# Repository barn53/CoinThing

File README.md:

# WhaleTicker
a coin ticker display

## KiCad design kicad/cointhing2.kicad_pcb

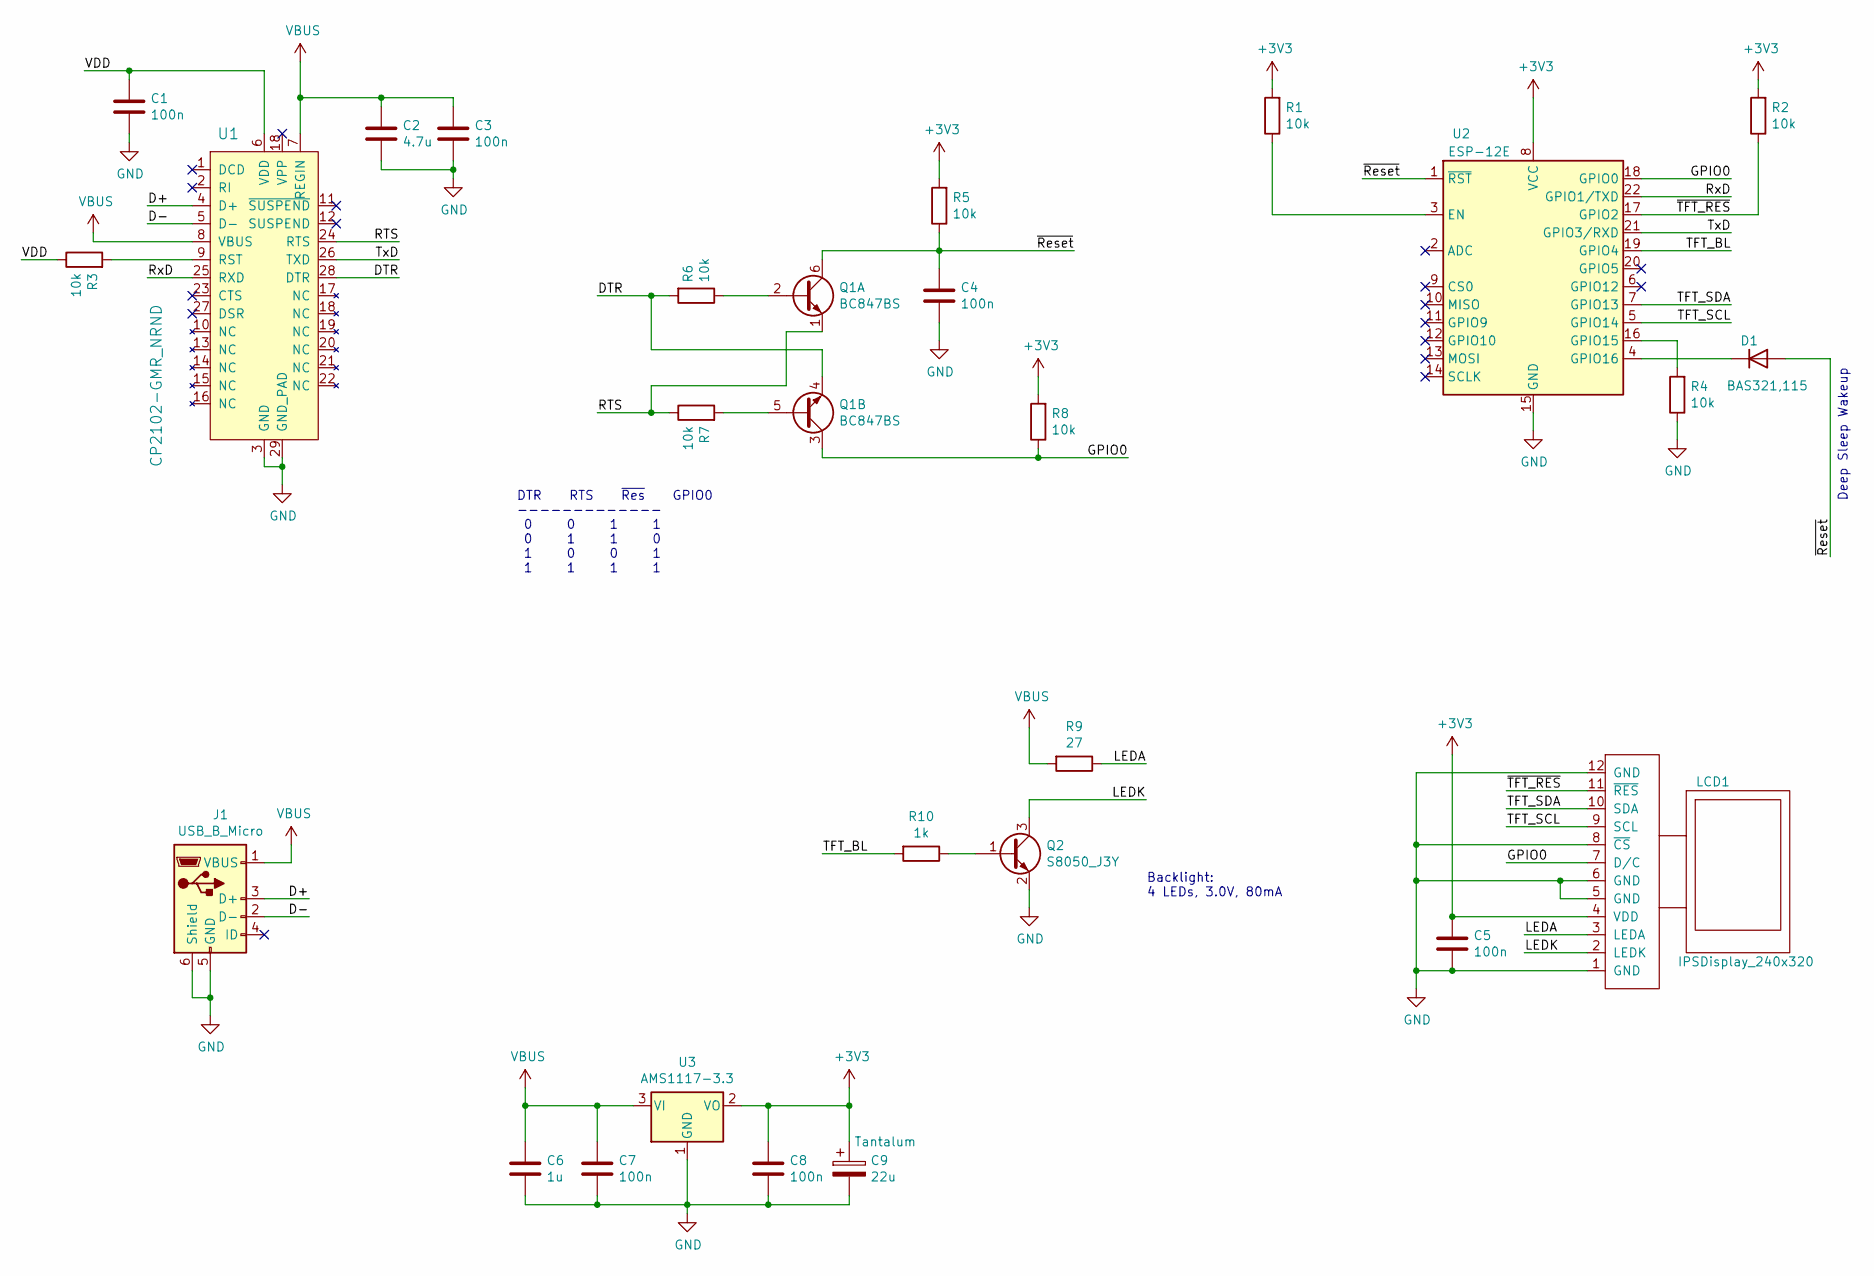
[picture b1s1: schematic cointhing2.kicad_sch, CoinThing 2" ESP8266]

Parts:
C1, C3, C4, C5, C7, C8: 100n; C_0603_1608Metric; LCSC C14663
C2: 4.7u; C_0603_1608Metric; LCSC C19666
C6: 1u; C_0603_1608Metric; LCSC C15849
C9: 22u; CP_EIA-3216-18_Kemet-A; LCSC C129272
D1: BAS321,115; D_SOD-323; LCSC C24372
J1: USB_B_Micro; MicroUSB_through_hole_fixing; LCSC3 C10418
LCD1: IPSDisplay_240x320; IPS_Display_240x320_FPC_105deg
Q1: BC847BS; SOT-363_SC-70-6; LCSC C8653
Q2: S8050_J3Y; SOT-23; LCSC C2146
R1, R2, R3, R4, R5, R6, R7, R8: 10k; R_0603_1608Metric; LCSC C25804
R9: 27; R_0603_1608Metric; LCSC C25190
R10: 1k; R_0603_1608Metric; LCSC C21190
U1: CP2102-GMR_NRND; QFN-28-1EP_5x5mm_P0.5mm_EP3.35x3.35mm; MPN CP2102-GMR; Digi-Key_PN 336-1160-1-ND
U2: ESP-12E; LCSC C82891
U3: AMS1117-3.3; SOT-223-3_TabPin2; LCSC C6186

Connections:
+3V3: C5.1, C8.1, C9.1, LCD1.4 (VDD), R1.2, R2.2, R5.2, R8.2, U2.8 (VCC), U3.2 (VO)
/D+: J1.3 (D+), U1.4 (D+)
/D-: J1.2 (D-), U1.5 (D-)
/DTR: Q1.4 (E2), R6.2, U1.28 (DTR)
/GPIO0: LCD1.7 (D/C), Q1.3 (C2), R8.1, U2.18 (GPIO0)
/LEDA: LCD1.3 (LEDA), R9.1
/LEDK: LCD1.2 (LEDK), Q2.3 (C)
/RTS: Q1.1 (E1), R7.1, U1.24 (RTS)
/RxD: U1.25 (RXD), U2.22 (GPIO1/TXD)
/TFT_BL: R10.2, U2.19 (GPIO4)
/TFT_SCL: LCD1.9 (SCL), U2.5 (GPIO14)
/TFT_SDA: LCD1.10 (SDA), U2.7 (GPIO13)
/TxD: U1.26 (TXD), U2.21 (GPIO3/RXD)
/VDD: C1.1, R3.1, U1.6 (VDD)
/~Reset: C4.1, D1.2 (A), Q1.6 (C1), R5.1, U2.1 (~RST)
/~TFT_RES: LCD1.11 (~RES), R2.1, U2.17 (GPIO2)
GND: C1.2, C2.2, C3.2, C4.2, C5.2, C6.2, C7.2, C8.2, C9.2, J1.5 (GND), J1.6 (Shield), LCD1.1 (GND), LCD1.5 (GND), LCD1.6 (GND), LCD1.8 (~CS), LCD1.12 (GND), Q2.2 (E), R4.1, U1.3 (GND), U1.29 (GND_PAD), U2.15 (GND), U3.1 (GND)
unnamed: Q1.2 (B1), R6.1
unnamed: Q1.5 (B2), R7.2
unnamed: Q2.1 (B), R10.1
unnamed: R1.1, U2.3 (EN)
unnamed: R3.2, U1.9 (RST)
unnamed: R4.2, U2.16 (GPIO15)
unnamed: D1.1 (K), U2.4 (GPIO16)
VBUS: C2.1, C3.1, C6.1, C7.1, J1.1 (VBUS), R9.2, U1.7 (REGIN), U1.8 (VBUS), U3.3 (VI)

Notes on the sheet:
DTR RTS ~{Res} GPIO0 ------------- 0 0 1 1 0 1 1 0 1 0 0 1 1 1 1 1
Deep Sleep Wakeup
Backlight: 4 LEDs, 3.0V, 80mA

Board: 2 copper layers, 30 parts (1 on the bottom side), 25 nets, no tracks yet.

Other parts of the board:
QR*****: https://github.com/barn53/CoinThing/tree/2inch; __github.com_barn53_CoinThing_tree_2inch
h1, h2: MountingHole

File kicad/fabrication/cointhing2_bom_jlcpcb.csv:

Comment,Designator,Footprint,LCSC
"4.7u","C2","Capacitor_SMD:C_0603_1608Metric","C19666"
"1u","C6","Capacitor_SMD:C_0603_1608Metric","C15849"
"100n","C1,C3,C4,C5,C7,C8","Capacitor_SMD:C_0603_1608Metric","C14663"
"22u","C9","Capacitor_Tantalum_SMD:CP_EIA-3216-18_Kemet-A","C129272"
"IPSDisplay_240x320","D1","barn53-kicad:IPS_Display_240x320_FPC_105deg",""
"USB_B_Micro","J1","barn53-kicad:MicroUSB_through_hole_fixing","C404969"
"BC847BS","Q1","Package_TO_SOT_SMD:SOT-363_SC-70-6","C8653"
"S8050_J3Y","Q2","Package_TO_SOT_SMD:SOT-23","C2146"
"1k","R11","Resistor_SMD:R_0603_1608Metric","C21190"
"10k","R1,R2,R3,R4,R5,R6,R7,R8,R10","Resistor_SMD:R_0603_1608Metric","C25804"
"10","R9","Resistor_SMD:R_0603_1608Metric","C22859"
"CP2102-GMR_NRND","U1","Package_DFN_QFN:QFN-28-1EP_5x5mm_P0.5mm_EP3.35x3.35mm","C6568"
"ESP-12E","U2","barn53-kicad:ESP-12E","C82891"
"AMS1117-3.3","U3","Package_TO_SOT_SMD:SOT-223-3_TabPin2","C6186"

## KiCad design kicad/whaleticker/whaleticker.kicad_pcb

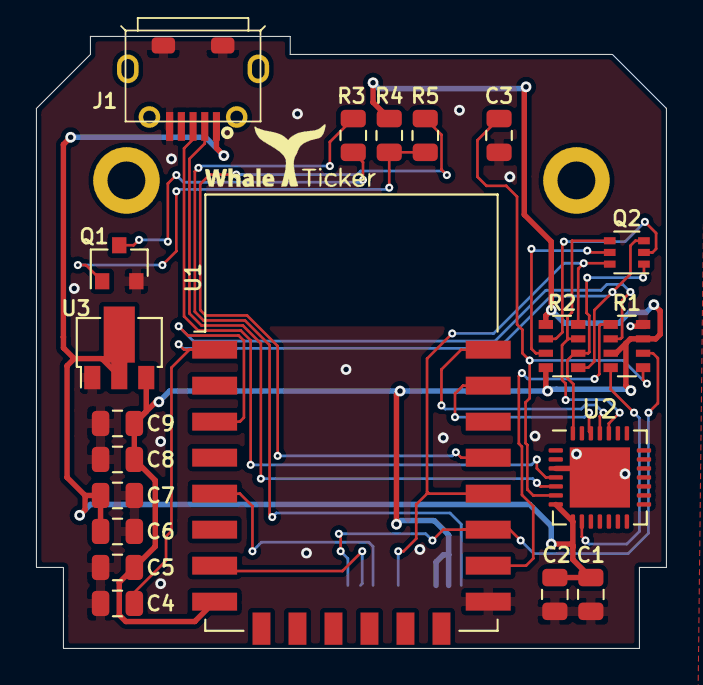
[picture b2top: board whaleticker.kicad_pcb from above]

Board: 2 copper layers, 35.0 x 34.0 mm, 21 parts (0 on the bottom side), 24 nets.

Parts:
C1, C3, C4, C5, C7, C8: 100n; C_0805_2012Metric
C2, C9: 4.7u; C_0805_2012Metric
C6: 1u; C_0805_2012Metric
D1: IPSDisplay_240x240; IPSDisplay_240x240_FPC_80deg
J1: USB_B_Micro; MicroUSB_through_hole_fixing
Q1: S8050_J3Y; SOT-23
Q2: PMBT2222AYS; SOT-363_SC-70-6
R1, R2: 10k; R_Array_Convex_4x0603
R3: 10; R_0805_2012Metric
R4: 10k; R_0805_2012Metric
R5: 1k; R_0805_2012Metric
U1: ESP-12E
U2: CP2102-GMR_NRND; QFN-28-1EP_5x5mm_P0.5mm_EP3.35x3.35mm
U3: BL8565; SOT-89-3

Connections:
+3V3: C5.1, C8.1, C9.1, D1.3, D1.4, R1.3, R1.7, R2.5, R2.8, R4.2, U1.8, U3.3
/D+: J1.3, U2.4
/D-: J1.2, U2.5
/DTR: Q2.1, R2.2, U2.28
/GPIO0: D1.7, Q2.6, R2.4, U1.18
/LEDK: D1.2, R3.1
/RTS: Q2.4, R2.3, U2.24
/RxD: U1.22, U2.25
/TFT_BL: R5.2, U1.19
/TFT_SCL: D1.9, U1.5
/TFT_SDA: D1.10, U1.7
/TxD: U1.21, U2.26
/VDD: C3.1, R1.1, U2.6
/~Reset: C4.1, Q2.3, R2.1, U1.1
/~TFT_RES: D1.11, R1.2, U1.17
GND: C1.2, C2.2, C3.2, C4.2, C5.2, C6.2, C7.2, C8.2, C9.2, D1.1, D1.5, D1.6, D1.8, D1.12, J1.5, J1.6, Q1.2, R1.4, U1.15, U2.3, U2.29, U3.1
unnamed: Q1.1, R4.1, R5.1
unnamed: Q1.3, R3.2
unnamed: Q2.2, R2.6
unnamed: Q2.5, R2.7
unnamed: R1.5, U1.16
unnamed: R1.6, U1.3
unnamed: R1.8, U2.9
VBUS: C1.1, C2.1, C6.1, C7.1, J1.1, U2.7, U2.8, U3.2

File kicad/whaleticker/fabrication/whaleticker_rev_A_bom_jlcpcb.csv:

Comment,Designator,Footprint,LCSC
"1u","C6","Capacitor_SMD:C_0805_2012Metric","C28323"
"100n","C1,C3,C4,C5,C7,C8","Capacitor_SMD:C_0805_2012Metric","C49678"
"4.7u","C2,C9","Capacitor_SMD:C_0805_2012Metric","C1779"
"IPSDisplay_240x240","D1","barn53-kicad:IPSDisplay_240x240_FPC_80deg",""
"USB_B_Micro","J1","barn53-kicad:MicroUSB_through_hole_fixing","C404969"
"S8050_J3Y","Q1","Package_TO_SOT_SMD:SOT-23","C2146"
"BC847BS,115","Q2","Package_TO_SOT_SMD:SOT-363_SC-70-6","C8653"
"10k","R1,R2","Resistor_SMD:R_Array_Convex_4x0603","C29718"
"10","R3","Resistor_SMD:R_0805_2012Metric","C17415"
"10k","R4","Resistor_SMD:R_0805_2012Metric","C17414"
"1k","R5","Resistor_SMD:R_0805_2012Metric","C17513"
"ESP-12E","U1","barn53-kicad:ESP-12E","C82891"
"CP2102-GMR_NRND","U2","Package_DFN_QFN:QFN-28-1EP_5x5mm_P0.5mm_EP3.35x3.35mm","C6568"
"BL8565","U3","Package_TO_SOT_SMD:SOT-89-3","C51826"

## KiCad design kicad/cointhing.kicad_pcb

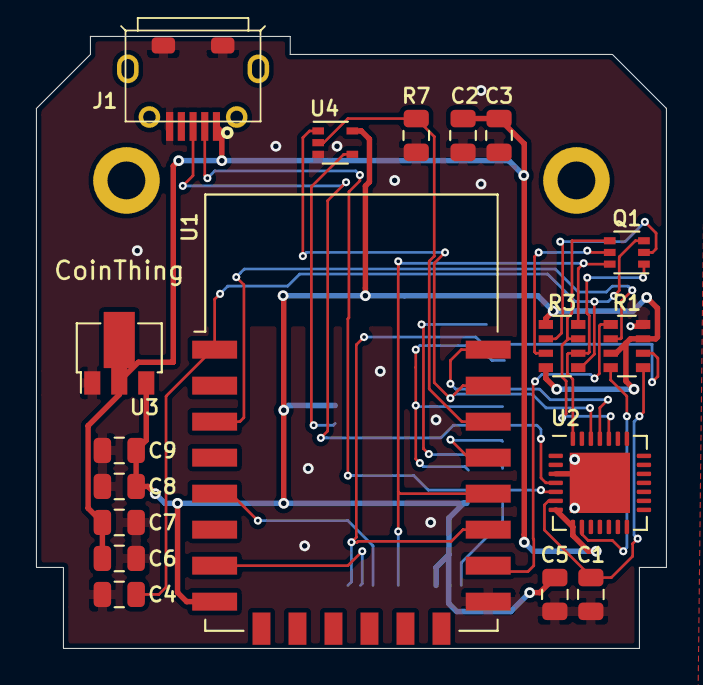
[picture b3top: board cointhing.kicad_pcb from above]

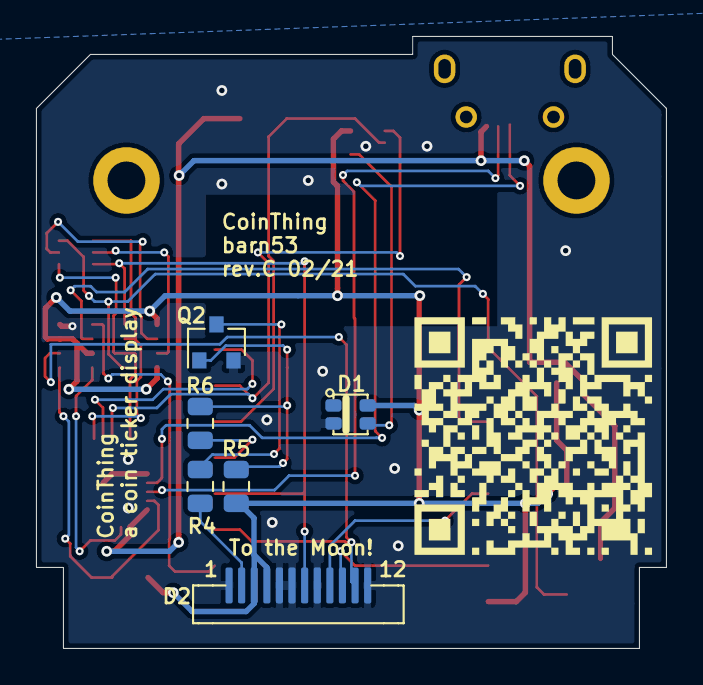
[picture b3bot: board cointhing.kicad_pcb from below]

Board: 2 copper layers, 35.0 x 34.0 mm, 25 parts (6 on the bottom side), 26 nets.

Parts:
C1, C3, C4, C5, C7, C8: 100n; C_0805_2012Metric
C2, C9: 4.7u; C_0805_2012Metric
C6: 1u; C_0805_2012Metric
D1: WS2812B-2020
D2: IPSDisplay_240x240; IPSDisplay_240x240_FPC_80deg
J1: USB_B_Micro; MicroUSB_through_hole_fixing
Q1: PUMX1; SOT-363_SC-70-6
Q2: S8050_J3Y; SOT-23
QR*****: https://barn53.github.io/CoinThing/; __barn53.github.io_CoinThing_
R1, R3: 10k; R_Array_Convex_4x0603
R4: 10; R_0805_2012Metric
R5, R7: 10k; R_0805_2012Metric
R6: 1k; R_0805_2012Metric
U1: ESP-12E
U2: CP2102-GMR_NRND; QFN-28-1EP_5x5mm_P0.5mm_EP3.35x3.35mm
U3: BL8565; SOT-89-3
U4: 74AHC1G08; SOT-353_SC-70-5

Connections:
+3V3: C5.1, C8.1, C9.1, D1.4, D2.3, D2.4, R1.3, R1.7, R3.5, R3.8, R5.2, U1.8, U3.3, U4.5
/D+: J1.3, U2.4
/D-: J1.2, U2.5
/DTR: Q1.1, R3.2, U2.28
/GPIO0: D2.7, Q1.6, R3.4, U1.18
/GPIO5: R7.1, U1.20, U4.2
/LEDK: D2.2, R4.1
/RTS: Q1.4, R3.3, U2.24
/RxD: U1.22, U2.25
/TFT_BL: R6.2, U1.19
/TFT_SCL: D2.9, U1.5
/TFT_SDA: D2.10, U1.7
/TxD: U1.21, U2.26, U4.1
/VDD: C1.1, R1.1, U2.6
/~Reset: C4.1, Q1.3, R3.1, U1.1
/~TFT_RES: D2.11, R1.2, U1.17
GND: C1.2, C2.2, C3.2, C4.2, C5.2, C6.2, C7.2, C8.2, C9.2, D1.2, D2.1, D2.5, D2.6, D2.8, D2.12, J1.5, J1.6, Q2.2, R1.4, R7.2, U1.15, U2.3, U2.29, U3.1, U4.3
unnamed: D1.3, U4.4
unnamed: Q1.2, R3.6
unnamed: Q1.5, R3.7
unnamed: Q2.1, R5.1, R6.1
unnamed: Q2.3, R4.2
unnamed: R1.5, U1.16
unnamed: R1.6, U1.3
unnamed: R1.8, U2.9
VBUS: C2.1, C3.1, C6.1, C7.1, J1.1, U2.7, U2.8, U3.2

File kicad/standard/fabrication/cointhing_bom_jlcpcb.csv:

Comment,Designator,Footprint,LCSC
"1u","C6","Capacitor_SMD:C_0805_2012Metric","C28323"
"100n","C1,C3,C4,C5,C7,C8","Capacitor_SMD:C_0805_2012Metric","C49678"
"4.7u","C2,C9","Capacitor_SMD:C_0805_2012Metric","C1779"
"IPSDisplay_240x240","D1","barn53-kicad:IPSDisplay_240x240_FPC_80deg",""
"USB_B_Micro","J1","barn53-kicad:MicroUSB_through_hole_fixing","C404969"
"S8050_J3Y","Q1","Package_TO_SOT_SMD:SOT-23","C2146"
"PMBT2222AYS","Q2","Package_TO_SOT_SMD:SOT-363_SC-70-6","C99140"
"10k","R1,R2","Resistor_SMD:R_Array_Convex_4x0603","C29718"
"10","R3","Resistor_SMD:R_0805_2012Metric","C17415"
"10k","R4","Resistor_SMD:R_0805_2012Metric","C17414"
"1k","R5","Resistor_SMD:R_0805_2012Metric","C17513"
"ESP-12E","U1","barn53-kicad:ESP-12E","C82891"
"CP2102-GMR_NRND","U2","Package_DFN_QFN:QFN-28-1EP_5x5mm_P0.5mm_EP3.35x3.35mm","C6568"
"BL8565","U3","Package_TO_SOT_SMD:SOT-89-3","C51826"

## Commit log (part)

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2021-07-18 changed PMBT2222AYS to BC847BS,115 (only BOM) - due to shortage at JLCPCB...
2021-07-24 new icons - first step
2021-07-24 tried 160MHz CPU clock
2021-07-24 renamed
2021-07-24 3M SPIFFS size, 160MHz CPU clock
2021-07-25 Added seftest
2021-07-25 perpared version 1.3.1
2021-07-25 minor
2021-07-26 moved *.html out of source/data
    To reduce memory for SPIFFS file system.
    Only the *.gz files will be generated in source/data
2021-07-26 fits in 2MB SPIFFS again
2021-07-26 prepare v1.4.0
2021-07-27 upload script 1.4.0: first erase flash
2021-07-29 Introduced better tracing
2021-07-29 Fixed a situation where no chart was drawn when multiple coins were displayed.
2021-07-29 added fonts to selftest
2021-07-31 updated submodule TFT_eSPI
2021-07-31 hardened browser update procedure
    Restart ESP up to 10 times, if WiFi is not connected in
    update mode.
    More verbose display messages on the status of the update
    replaced ESP.reset() with ESP.restart()
2021-08-01 further improved waiting for WiFi when preparing update
    no longer restart loop (which looks ugly and faulty), but wait in a for loop for connection up to 5sec.
2021-08-01 prepare version 1.4.2
2021-08-02 added version v1.2.2 to doc
2021-08-06 serial monitor
2021-09-07 rotated voltage regulator 180 deg
2021-09-07 minor modifications
    - a bit more room for display
    - DisplayHalter a bit more room
2021-09-13 test error check
2021-09-13 check info
2021-09-13 used F() for json keys
2021-09-13 WiFi connect from optional file /wifi.json
    simplifies device preparation
2021-09-13 deleted source/data/rename_to_wifi.json
2021-09-13 updated solder stand
2021-09-13 admin with wifi.json
2021-09-15 pinned espressif8266 platform to 2.6.3
2021-11-14 CoinThing -> WhaleTicker
2021-11-14 submodule
2021-11-18 minor changes
2021-11-18 removed submodules in favor of PlatformIO lib_deps
2021-11-23 updated docs
2021-11-23 initial steps to the 2" version of cointhing PCB
2021-11-23 minr
2021-11-25 finished PCB rev.A
2021-11-29 Wired deep sleep wakeup
2021-11-30 Changed PCB to WhaleTicker
2021-11-30 docs 2inch
2021-11-30 changed doc
2021-11-30 deleted docs from main branch
2021-11-30 deleted docs from whaleticker branch
2021-11-30 deleted docs from v1.2 branch
2021-11-30 deleted eveything but docs from pages branch
2021-11-30 html files: 2"
2021-12-01 html: 2021 -> 2022
2021-12-05 Update backlight supply
2021-12-05 early welcome screen
2021-12-05 moved trending button
2021-12-05 Updated for version 1.5.0
2021-12-07 disarm check.json
2021-12-07 added whaleticker logo
2021-12-07 check.json error
2021-12-07 check.json info
2021-12-07 check.json disarm
2021-12-08 started with gecko api test
2021-12-08 added fake data
2021-12-10 schematics A3 -> A4
2021-12-10 again minor quirks
2021-12-13 Create LICENSE
2021-12-21 removed older 3d models
2021-12-21 updated case 3d files
2021-12-27 Front with lowering instead of chamfer
2021-12-28 Modified Back to thin wall thickness to minimize gap and rework
2022-01-03 removed unecesary stuff
2022-01-03 removed
2022-01-04 added nose to the display halter light to simplify removing a mounted display
2022-01-11 added more space for display halter
2022-01-12 new front version project
2022-01-12 colorset admin and selftest
2022-01-19 KiCAD 6, modified schematics
2022-01-19 KiCAD 6
2022-01-22 Set Gecko Fake Server with URL
2022-01-22 Introduced last http code
    output it on screen when chart update failed
2022-01-23 PCB update
2022-01-24 PCB rev.B ready
2022-02-08 number format: compact zeroes 0.00012 -> 3z12
    Is currently always active - settings with a later change!
    Added unit tests for number format
2022-02-08 number format: use gecko_t instead of float
2022-02-09 fixed formatNumber()
    added unit tests
2022-02-09 further improved compactZeroes
2022-02-10 finished numberFormat()
    fixed 4 digits after z
    leading currency symbol
    completed unit tests
2022-02-10 allow update even with wifi.json file
2022-03-03 2020 -> 2022
2022-03-03 fixed diff marker
2022-03-03 number format: 5 decimal places for values < 1
2022-03-03 fixed unit tests
2022-03-03 fixed unit test
2022-03-03 settings: sort out coins with id, name or symbol of length 0
2022-03-15 fixed displaying wifi not connected icon
    (cherry picked from commit 8c19f4a00cd41273cea0ec9c8663ca120e47a022)
2022-03-17 added url to set fake gecko api
2022-03-17 updated ArduinoJson to 8.19.3
    This version uses double as default type.
    Improved formatting of double numbers
    Added unit test for this
2022-04-12 Changes for Version 1.6
2022-04-19 Introduced startup sequence to reset CoinThing
2022-04-19 current coin indicator a bit wider
2022-04-20 also show connection info on fail screen
2022-04-21 peacock color
2022-04-21 Introduced startup sequence to reset CoinThing
    (cherry picked from commit 3b731db0c2e957b76fd3b910b83f889d49fac13e)
2022-04-21 current coin indicator a bit wider
    (cherry picked from commit 6cd59a1dc1f3f380dc371853556048dbc063b370)
2022-04-21 also show connection info on fail screen
    (cherry picked from commit df75c0870a5c48500b338dc0c3352d2e032f0020)
2022-04-21 Version 1.6.1
2022-04-21 minor fix for powerup and firmware update
2022-04-21 modified powerup sequence indicator position
2022-04-21 modified powerup sequence indicator position
    (cherry picked from commit e1c656cd3e328b2216651f081b7de5965b14ae07)
2022-04-21 removed #include
2022-07-12 moved favicon to barn53/assets
2022-07-17 fixed __VA_ARGS__ to ##__VA_ARGS__
2022-07-17 fixed __VA_ARGS__ to ##__VA_ARGS__
    (cherry picked from commit b5bc0dfe91e4313524575b7a09fdd47174999476)
2022-07-17 added upload file for wifi spiffs
2022-07-17 Shorter host name - it did not fit to the startup scrren
2022-07-21 changes download assets branch to wt_v2
2022-07-28 Get assets from new WhaleTicker gihub account
2022-07-31 show a pause symbol when HTTP code 429 received and wait 120 secs
    Do no longer show 'Update chart failed!' in this case - was irritating
2022-07-31 prepare large number support for market cap and volume
    (cherry picked from commit d253ad52f1b5aba6df34d3480c6d11985746a95d)
2022-08-03 fixed help text for fake gecko server
2022-08-03 modified the HTTP 429 behavior again
2022-08-03 prepare version v2.6.2
2022-08-05 Append reason to pipedream
2022-08-05 Large rework:
    - Pro API as fallback for HTTP 429 on free API
    - encryption and stuff
    - pipedream info
    - Reduced requests by a third (do not fetch after prefetch)
2022-08-06 reduce wait times for HTTP 429 related stuff when fake gecko server is active
2022-08-06 prevent too many requests on a more easy way
2022-08-06 Rework from whaleticker:
    - pipedream info
    - Reduced requests by one third (do not fetch after prefetch)
    - prevent too many requests on a more easy way
2022-08-07 introduced json store
    Base64 had problems under Windows (include file upper/lower case conflicts with framework base64.h)
    -> incorporated into utils...
    Expanded unit tests
2022-08-07 introduced json store
    Expanded unit tests
    (cherry picked from commit d054b08ca381f5c14191eaba22938fc2047d6aca)
2022-08-07 added secrets folder
2022-08-07 cool pre/post actions for building firmware and spiffs
2022-08-07 removed __pycache__
2022-08-07 minor fixes with build environment
2022-08-07 work with environment inheritance
2022-08-07 also copy keyfile
2022-08-08 utilize secrets api and related stuff
2022-08-08 refined deliver scripts again
    - create a version folder in assets/
    - create upload scripts
    - copy .html.gz files and version information for later html updates
    (cherry picked from commit 4601b4552d8b077384bd539cd35c3fb68bfffcba)
2022-08-08 moved Base64 to own file
2022-08-08 changed init screen show time
2022-08-08 copy settings.json to data with develop build target
    (cherry picked from commit ee496fccb6486cdfc3db58b2f14d6ed183264c21)
2022-08-08 Settings::getSettings() now serializes without whitespace an newlines
2022-08-09 action/set?proapi to en/disable pro api
2022-08-10 moved common classes to extern
2022-08-10 moved common classes to extern
    (cherry picked from commit 1a4b2a96eca85b7c3301aee2493c16c6c7e37044)
2022-08-10 added 429-pause to osd
2022-09-21 develop build without pipedream
2022-09-21 develop build without pipedream
    (cherry picked from commit 6ce42dbcd30e413f2a368cadf2c9e129605afb6c)
2022-09-21 fix build scripts
    (cherry picked from commit eaf610d5b5e04f4b380c88a93a5b6ec305139e88)
2022-09-25 fixed string
2022-09-25 fixed string
    (cherry picked from commit a90f4da8ff50700d73168aad5288885835ca6569)
2022-09-25 actualized some icons
    removed some icons to save SPIFFS space
    (cherry picked from commit 319159f832fd1ce608f9d06cf44d07ff565a5d2b)
2022-09-26 second currency as value, market cap., volume
2022-09-30 market cap and volume
    (cherry picked from commit 136a39a9fe62b24611c8642f6fe69f4635bc0304)
2022-09-30 second currency as value, market cap., volume
    (cherry picked from commit 88d6b8c092e114d02b8adcd50dccccd9c5c1da2f)
    (cherry picked from commit 0ed9646137c4fc2d35868a35e7de2c3f68ba33eb)
2022-09-30 Disable Pro API when no apikeycheck pipedream url length
2022-09-30 Check pipedream URL length
    (cherry picked from commit 9e221887defbdb984f2ece5b89824d65a29fa7fc)
2022-10-02 auto year in html footers
2022-10-02 auto year in html footers
    (cherry picked from commit a4c34a01aaabd82a2707d8b4679a6e0927e1fd56)
    (cherry picked from commit 580d08f78008855fa163459d1e8202bf67dd9db9)
2022-10-05 create secrets.json out of one source
2022-10-05 separate deliveries in named directories
2022-10-05 separate deliveries in named directories
    (cherry picked from commit c83bcff99753ae1148786a11979bcfd4158dde35)
2022-10-30 Schematic: new diode from GPIO16 to RESET
    In order for the deep sleep wake up will work with the auto programming circuit
2022-11-27 added PLU.bmp
2022-11-30 Introduce number format with less decimal places
2022-11-30 introduced down/up indicating dots
2023-01-19 Fixed problem with null values in CoinGecko response
    JSON null values in the response from CoinGecko led to a
    retry fetch loop until HTTP code 429 was issued, which in turn
    blocked the device.
    One known coin, that has null values is UNKAI
2023-02-13 added secrets/rename_to_secrets.json
    To build the project rename this file to secrets/secrets.json
    You can store your WiFi credentials in this file, to avoid connecting via WiFiManager
2023-02-17 Fixed problem with null values in CoinGecko response
    JSON null values in the response from CoinGecko led to a
    retry fetch loop until HTTP code 429 was issued, which in turn
    blocked the device.
    One known coin, that has null values is UNKAI
    (cherry picked from commit 0422f1181b756152056e9e0420aea79c33a01bdb)
2023-02-17 added secrets/rename_to_secrets.json
    To build the project rename this file to secrets/secrets.json
    You can store your WiFi credentials in this file, to avoid connecting via WiFiManager
    (cherry picked from commit 181be98fce3f1ac46377e65208d4eb1107ff6aad)
2023-09-13 dto.
2023-09-26 recreated 3d print files
2023-10-12 create colorset file in SPIFFs
2023-10-13 .gitignore colorset
2023-10-28 remove selftest
2023-10-28 added initial coincap.rest
2023-11-18 fixed problem when secrets.json contains invalid WiFi credentials
    (cherry picked from commit c69196ce7c08bf8ad0fdb0abe41389098595d0a2)
2023-11-19 remove selftest
    (cherry picked from commit 9d45302e0fe49d1e91799680b35ef728af9123da)
2023-11-19 s/bightness/brightness/
2023-11-19 introduced cg proxy server
    (cherry picked from commit b52a1743046d3bc0a6e59e8039fa442c63f6a61e)
2023-11-22 proxy wih keys, prepare2 scipt
